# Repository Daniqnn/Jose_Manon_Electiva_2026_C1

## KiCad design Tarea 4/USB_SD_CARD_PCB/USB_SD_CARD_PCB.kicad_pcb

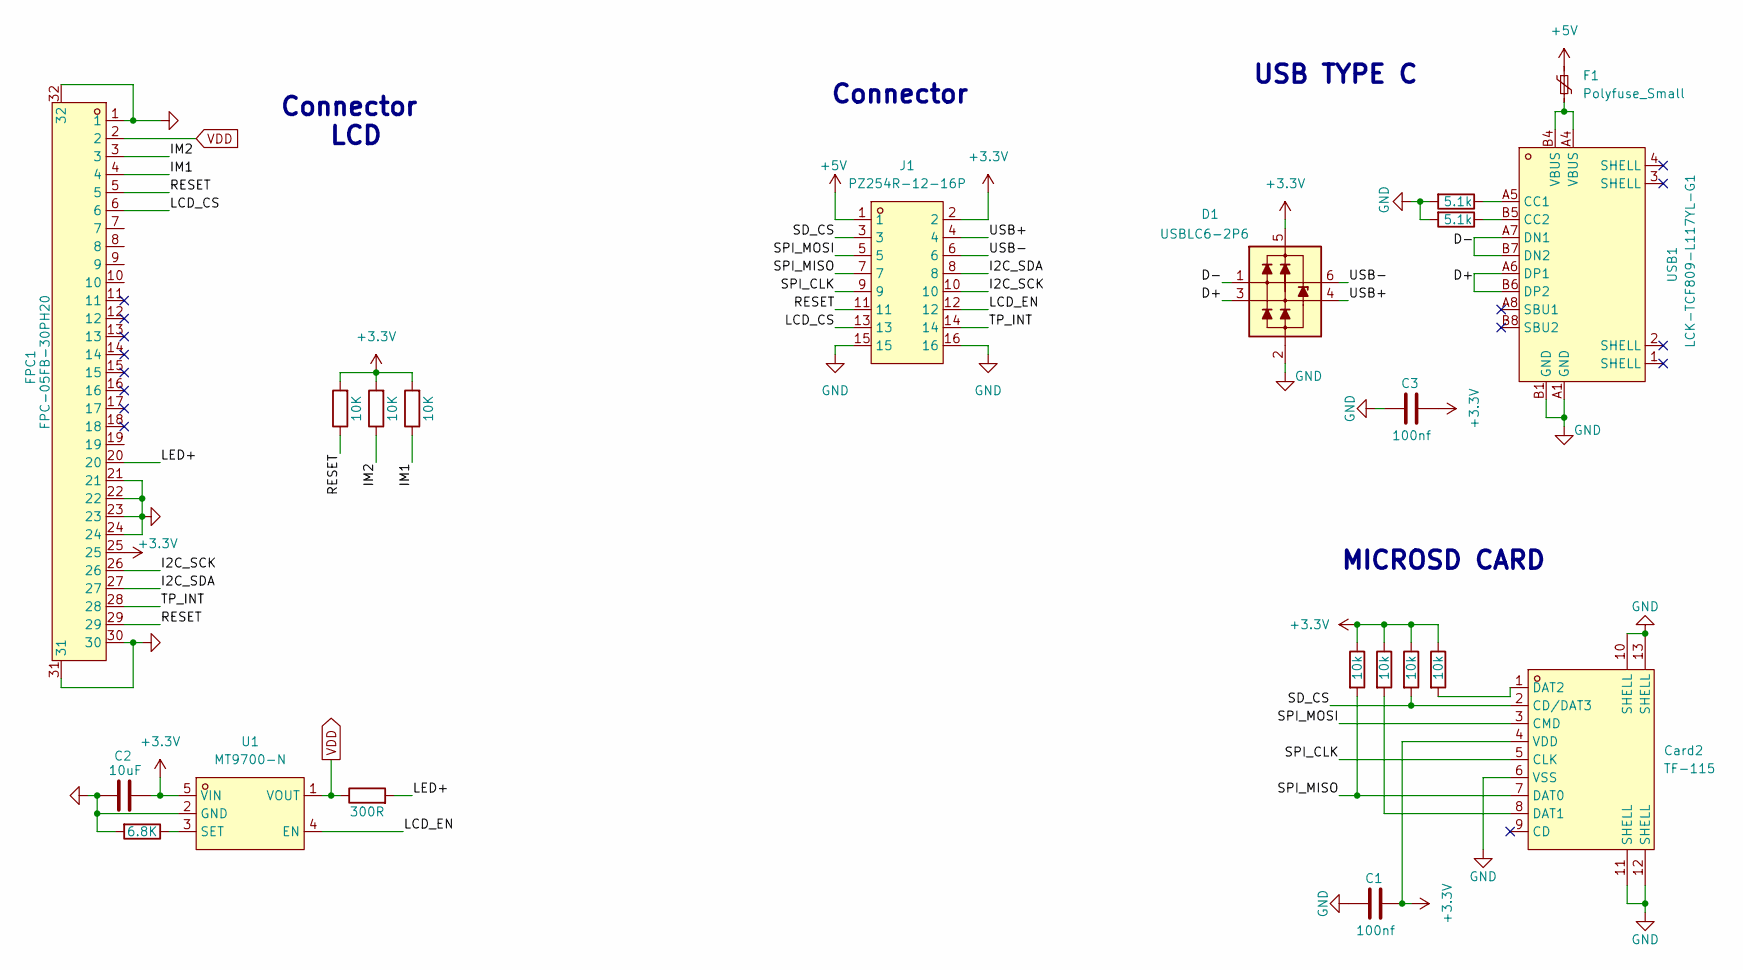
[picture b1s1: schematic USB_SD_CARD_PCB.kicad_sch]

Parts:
C1, C3: 100nf; C_0805_2012Metric; LCSC C710980
C2: 10uF; C_0201_0603Metric
Card2: TF-115; TF-SMD_TF-115; LCSC Part C266620
D1: USBLC6-2P6; SOT-666
F1: Polyfuse_Small; Fuse_0805_2012Metric
FPC1: FPC-05FB-30PH20; FPC-SMD_30P-P0.50_FPC-05FB-30PH20; LCSC Part C2856833
J1: PZ254R-12-16P; HDR-TH_16P-P2.54-H-M-R2-C8-S2.54; LCSC Part C492436
R1, R2: 5.1k; R_0805_2012Metric; LCSC C2930296
R3, R4, R5, R6: 10k; R_0603_1608Metric; LCSC C2930296
R7: 6.8K; R_0603_1608Metric; LCSC C2930296
R8: 300R; R_0603_1608Metric; LCSC C2930296
R9, R10, R11: 10K; R_0603_1608Metric; LCSC C2930296
U1: MT9700-N; SOT-23-5_L2.9-W1.6-P0.95-LS2.9-BL; LCSC Part C42441843
USB1: LCK-TCF809-L117YL-G1; USB-C-SMD_LCK-TCF809-L117YL-G1; LCSC Part C50380973

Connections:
+3.3V: C1.1, C2.1, C3.1, Card2.4 (VDD), D1.5 (VP), FPC1.25, J1.2, R3.1, R4.1, R5.1, R6.1, R9.2, R10.2, R11.2, U1.5 (VIN)
+5V: F1.1, J1.1
/D+: D1.3 (L2), USB1.A6 (DP1), USB1.B6 (DP2)
/D-: D1.1 (L1), USB1.A7 (DN1), USB1.B7 (DN2)
/I2C_SCK: FPC1.26, J1.10
/I2C_SDA: FPC1.27, J1.8
/IM1: FPC1.4, R11.1
/IM2: FPC1.3, R10.1
/LCD_CS: FPC1.6, J1.13
/LCD_EN: J1.12, U1.4 (EN)
/LED+: FPC1.20, R8.2
/RESET: FPC1.5, FPC1.29, J1.11, R9.1
/SD_CS: Card2.2 (CD/DAT3), J1.3, R4.2
/SPI_CLK: Card2.5 (CLK), J1.9
/SPI_MISO: Card2.7 (DAT0), J1.7, R6.2
/SPI_MOSI: Card2.3 (CMD), J1.5
/TP_INT: FPC1.28, J1.14
/USB+: D1.4 (L2), J1.4
/USB-: D1.6 (L1), J1.6
GND: C1.2, C2.2, C3.2, Card2.6 (VSS), Card2.10 (SHELL), Card2.11 (SHELL), Card2.12 (SHELL), Card2.13 (SHELL), D1.2 (VN), FPC1.1, FPC1.21, FPC1.22, FPC1.23, FPC1.24, FPC1.30, FPC1.31, FPC1.32, J1.15, J1.16, R1.2, R2.2, R7.2, U1.2 (GND), USB1.A1 (GND), USB1.B1 (GND)
unnamed: Card2.8 (DAT1), R5.2
unnamed: Card2.1 (DAT2), R3.2
unnamed: F1.2, USB1.A4 (VBUS), USB1.B4 (VBUS)
unnamed: R7.1, U1.3 (SET)
unnamed: R1.1, USB1.A5 (CC1)
unnamed: R2.1, USB1.B5 (CC2)
VDD: FPC1.2, R8.1, U1.1 (VOUT)

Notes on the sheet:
Connector LCD
USB TYPE C
MICROSD CARD
Connector

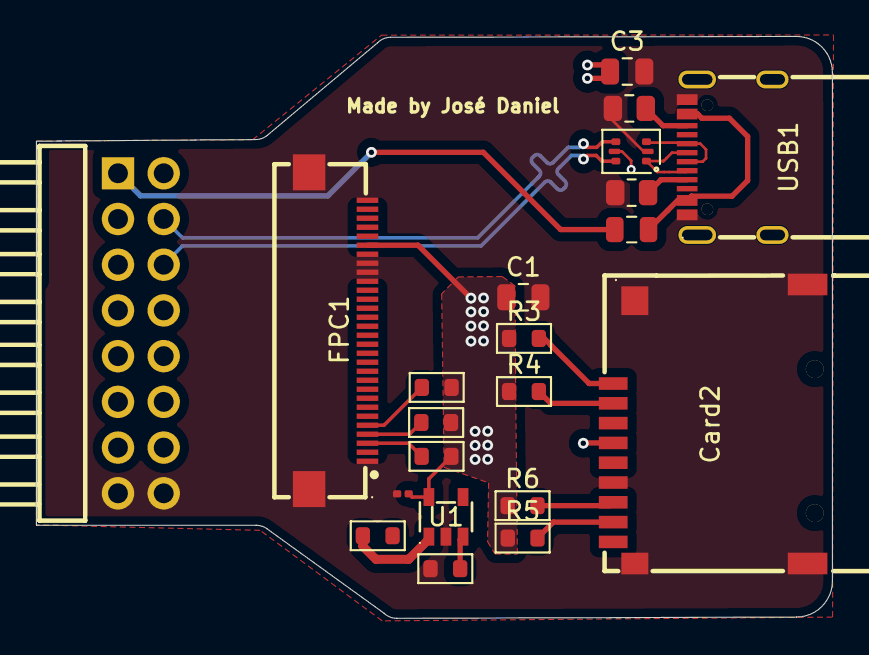
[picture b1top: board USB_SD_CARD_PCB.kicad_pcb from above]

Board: 4 copper layers, 44.2 x 32.3 mm, 21 parts (0 on the bottom side), 27 nets.

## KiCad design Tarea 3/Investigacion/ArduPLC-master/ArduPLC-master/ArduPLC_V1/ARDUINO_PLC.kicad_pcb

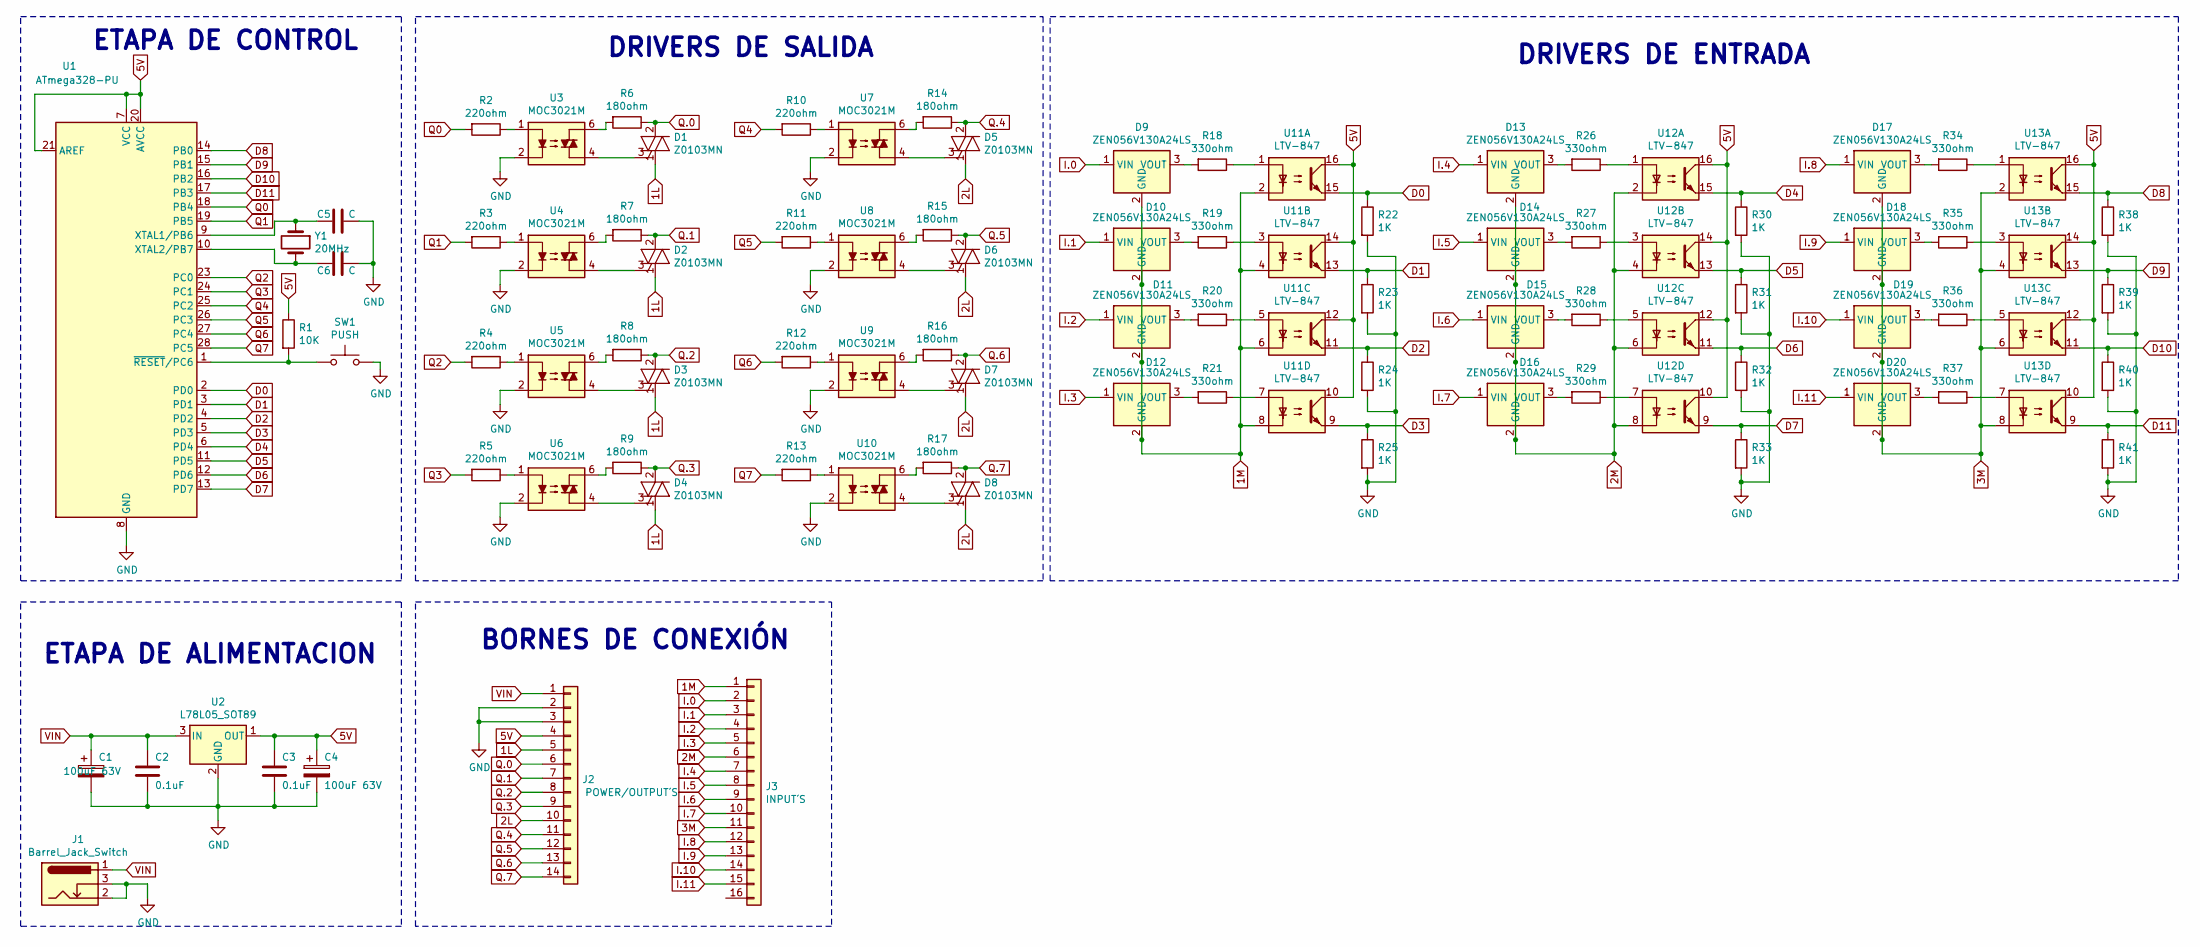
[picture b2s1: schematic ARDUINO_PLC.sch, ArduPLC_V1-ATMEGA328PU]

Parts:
C1, C4: 100uF 63V; CP_Radial_D8.0mm_P3.80mm
C2, C3: 0.1uF; C_Disc_D5.0mm_W2.5mm_P2.50mm
C5, C6: C; C_Disc_D5.0mm_W2.5mm_P2.50mm
D1, D2, D3, D4, D5, D6, D7, D8: Z0103MN; SOT-223
D9, D10, D11, D12, D13, D14, D15, D16, D17, D18, D19, D20: ZEN056V130A24LS; Littelfuse_PolyZen-LS
J1: Barrel_Jack_Switch; BarrelJack_Horizontal
J2: POWER/OUTPUT´S; Altech_AK300_1x14_P5.00mm_45-Degree
J3: INPUT´S; Altech_AK300_1x16_P5.00mm_45-Degree
R1: 10K; R_Axial_DIN0204_L3.6mm_D1.6mm_P1.90mm_Vertical
R2, R3, R4, R5, R10, R11, R12, R13: 220ohm; R_Axial_DIN0204_L3.6mm_D1.6mm_P1.90mm_Vertical
R6, R7, R8, R9, R14, R15, R16, R17: 180ohm; R_Axial_DIN0204_L3.6mm_D1.6mm_P1.90mm_Vertical
R18, R19, R20, R21, R26, R27, R28, R29, R34, R35, R36, R37: 330ohm; R_Axial_DIN0204_L3.6mm_D1.6mm_P1.90mm_Vertical
R22, R23, R24, R25, R30, R31, R32, R33, R38, R39, R40, R41: 1K; R_Axial_DIN0204_L3.6mm_D1.6mm_P1.90mm_Vertical
SW1: PUSH; Button_6mm
U1: ATmega328-PU; DIP-28_W7.62mm
U2: L78L05_SOT89; SOT-89-3
U3, U4, U5, U6, U7, U8, U9, U10: MOC3021M; DIP-6_W7.62mm_LongPads
U11, U12, U13: LTV-847; DIP-16_W7.62mm
Y1: 20MHz; Crystal_HC52-U_Vertical

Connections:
1L: D1.1 (A1), D2.1 (A1), D3.1 (A1), D4.1 (A1), J2.5
1M: D9.2 (GND), D10.2 (GND), D11.2 (GND), D12.2 (GND), J3.1, U11.2, U11.4, U11.6, U11.8
2L: D5.1 (A1), D6.1 (A1), D7.1 (A1), D8.1 (A1), J2.10
2M: D13.2 (GND), D14.2 (GND), D15.2 (GND), D16.2 (GND), J3.6, U12.2, U12.4, U12.6, U12.8
3M: D17.2 (GND), D18.2 (GND), D19.2 (GND), D20.2 (GND), J3.11, U13.2, U13.4, U13.6, U13.8
5V: C3.1, C4.1, J2.4, R1.1, U1.7 (VCC), U1.20 (AVCC), U1.21 (AREF), U2.1 (OUT), U11.10, U11.12, U11.14, U11.16, U12.10, U12.12, U12.14, U12.16, U13.10, U13.12, U13.14, U13.16
D0: R22.1, U1.2 (PD0), U11.15
D1: R23.1, U1.3 (PD1), U11.13
D2: R24.1, U1.4 (PD2), U11.11
D3: R25.1, U1.5 (PD3), U11.9
D4: R30.1, U1.6 (PD4), U12.15
D5: R31.1, U1.11 (PD5), U12.13
D6: R32.1, U1.12 (PD6), U12.11
D7: R33.1, U1.13 (PD7), U12.9
D8: R38.1, U1.14 (PB0), U13.15
D9: R39.1, U1.15 (PB1), U13.13
D10: R40.1, U1.16 (PB2), U13.11
D11: R41.1, U1.17 (PB3), U13.9
GND: C1.2, C2.2, C3.2, C4.2, C5.1, C6.1, J1.2, J1.3, J2.2, J2.3, R22.2, R23.2, R24.2, R25.2, R30.2, R31.2, R32.2, R33.2, R38.2, R39.2, R40.2, R41.2, SW1.2, U1.8 (GND), U1.22 (GND), U2.2 (GND), U3.2, U4.2, U5.2, U6.2, U7.2, U8.2, U9.2, U10.2
I.0: D9.1 (VIN), J3.2
I.1: D10.1 (VIN), J3.3
I.2: D11.1 (VIN), J3.4
I.3: D12.1 (VIN), J3.5
I.4: D13.1 (VIN), J3.7
I.5: D14.1 (VIN), J3.8
I.6: D15.1 (VIN), J3.9
I.7: D16.1 (VIN), J3.10
I.8: D17.1 (VIN), J3.12
I.9: D18.1 (VIN), J3.13
I.10: D19.1 (VIN), J3.14
I.11: D20.1 (VIN), J3.15
unnamed: C5.2, U1.9 (XTAL1/PB6), Y1.1
unnamed: C6.2, U1.10 (XTAL2/PB7), Y1.2
unnamed: D1.3 (G), U3.4
unnamed: D2.3 (G), U4.4
unnamed: D3.3 (G), U5.4
unnamed: D4.3 (G), U6.4
unnamed: D5.3 (G), U7.4
unnamed: D6.3 (G), U8.4
unnamed: D7.3 (G), U9.4
unnamed: D8.3 (G), U10.4
unnamed: D9.3 (VOUT), R18.2
unnamed: D10.3 (VOUT), R19.2
unnamed: D11.3 (VOUT), R20.2
unnamed: D12.3 (VOUT), R21.2
unnamed: D13.3 (VOUT), R26.2
unnamed: D14.3 (VOUT), R27.2
unnamed: D15.3 (VOUT), R28.2
unnamed: D16.3 (VOUT), R29.2
unnamed: D17.3 (VOUT), R34.2
unnamed: D18.3 (VOUT), R35.2
unnamed: D19.3 (VOUT), R36.2
unnamed: D20.3 (VOUT), R37.2
unnamed: R1.2, SW1.1, U1.1 (~RESET~/PC6)
unnamed: R2.1, U3.1
unnamed: R3.1, U4.1
unnamed: R4.1, U5.1
unnamed: R5.1, U6.1
unnamed: R6.2, U3.6
unnamed: R7.2, U4.6
unnamed: R8.2, U5.6
unnamed: R9.2, U6.6
unnamed: R10.1, U7.1
unnamed: R11.1, U8.1
unnamed: R12.1, U9.1
unnamed: R13.1, U10.1
unnamed: R14.2, U7.6
unnamed: R15.2, U8.6
unnamed: R16.2, U9.6
unnamed: R17.2, U10.6
unnamed: R18.1, U11.1
unnamed: R19.1, U11.3
unnamed: R20.1, U11.5
unnamed: R21.1, U11.7
unnamed: R26.1, U12.1
unnamed: R27.1, U12.3
unnamed: R28.1, U12.5
unnamed: R29.1, U12.7
unnamed: R34.1, U13.1
unnamed: R35.1, U13.3
unnamed: R36.1, U13.5
unnamed: R37.1, U13.7
Q0: R2.2, U1.18 (PB4)
Q1: R3.2, U1.19 (PB5)
Q2: R4.2, U1.23 (PC0)
Q3: R5.2, U1.24 (PC1)
Q4: R10.2, U1.25 (PC2)
Q5: R11.2, U1.26 (PC3)
Q6: R12.2, U1.27 (PC4)
Q7: R13.2, U1.28 (PC5)
Q.0: D1.2 (A2), D1.4 (A4), J2.6, R6.1
Q.1: D2.2 (A2), D2.4 (A4), J2.7, R7.1
Q.2: D3.2 (A2), D3.4 (A4), J2.8, R8.1
Q.3: D4.2 (A2), D4.4 (A4), J2.9, R9.1
Q.4: D5.2 (A2), D5.4 (A4), J2.11, R14.1
Q.5: D6.2 (A2), D6.4 (A4), J2.12, R15.1
Q.6: D7.2 (A2), D7.4 (A4), J2.13, R16.1
Q.7: D8.2 (A2), D8.4 (A4), J2.14, R17.1
VIN: C1.1, C2.1, J1.1, J2.1, U2.3 (IN)

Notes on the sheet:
ETAPA DE CONTROL
DRIVERS DE SALIDA
DRIVERS DE ENTRADA
ETAPA DE ALIMENTACION
BORNES DE CONEXIÓN

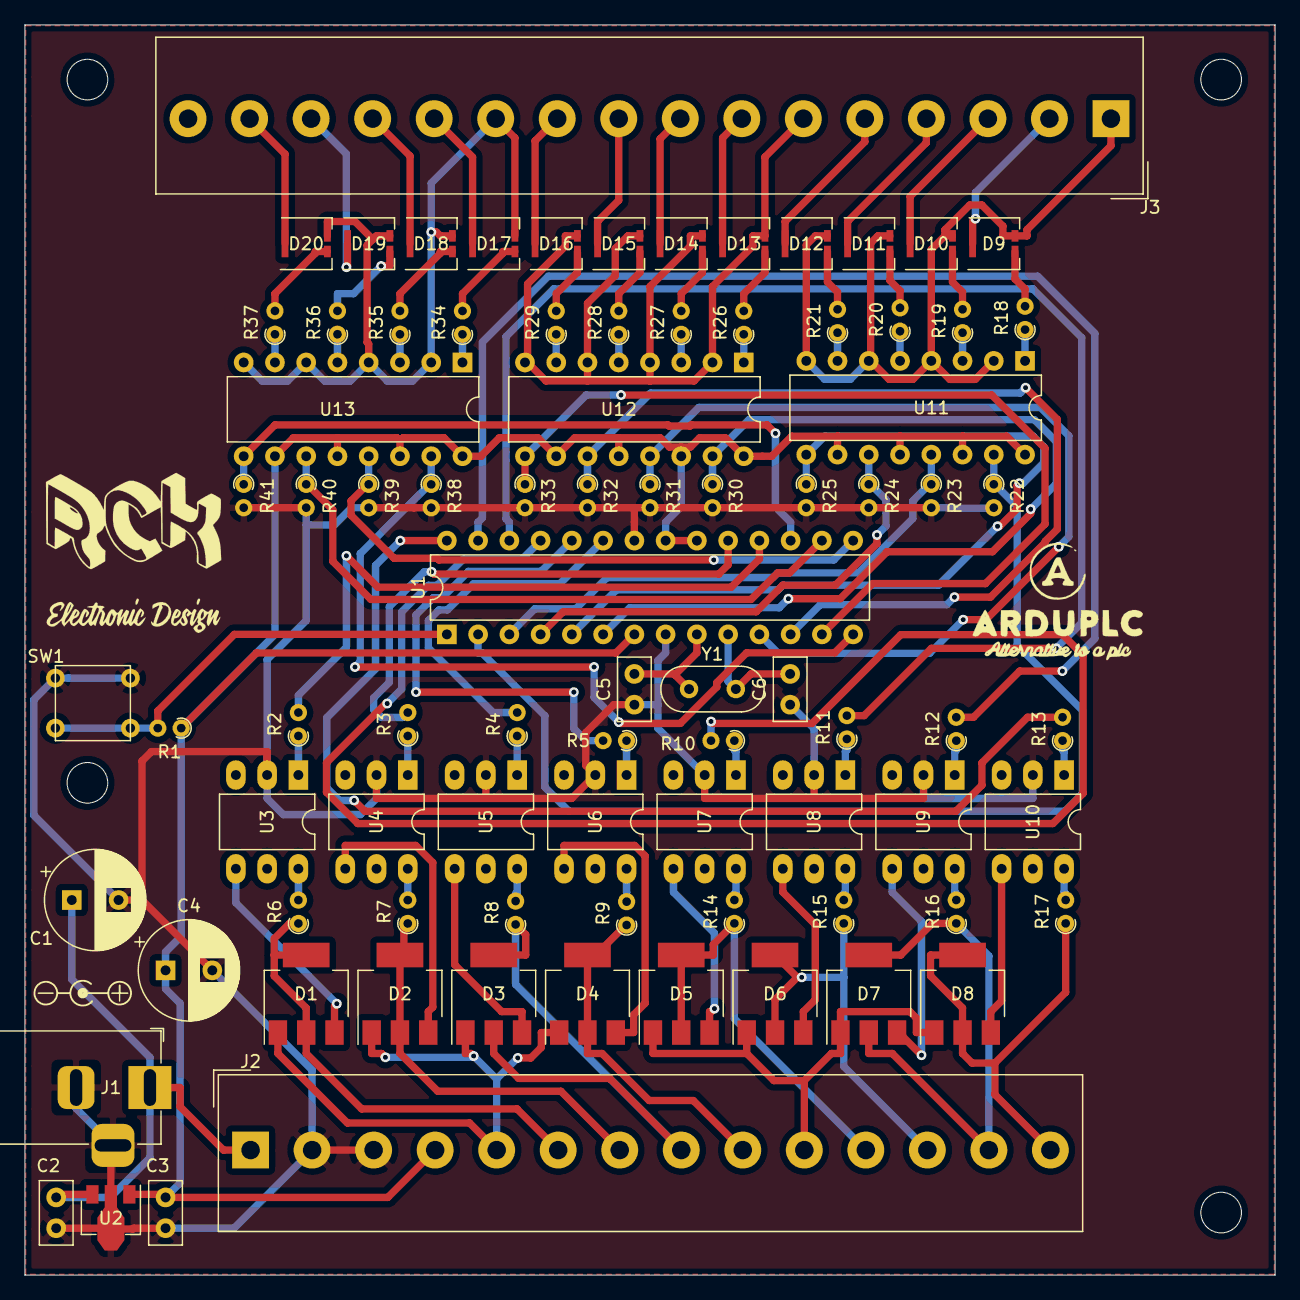
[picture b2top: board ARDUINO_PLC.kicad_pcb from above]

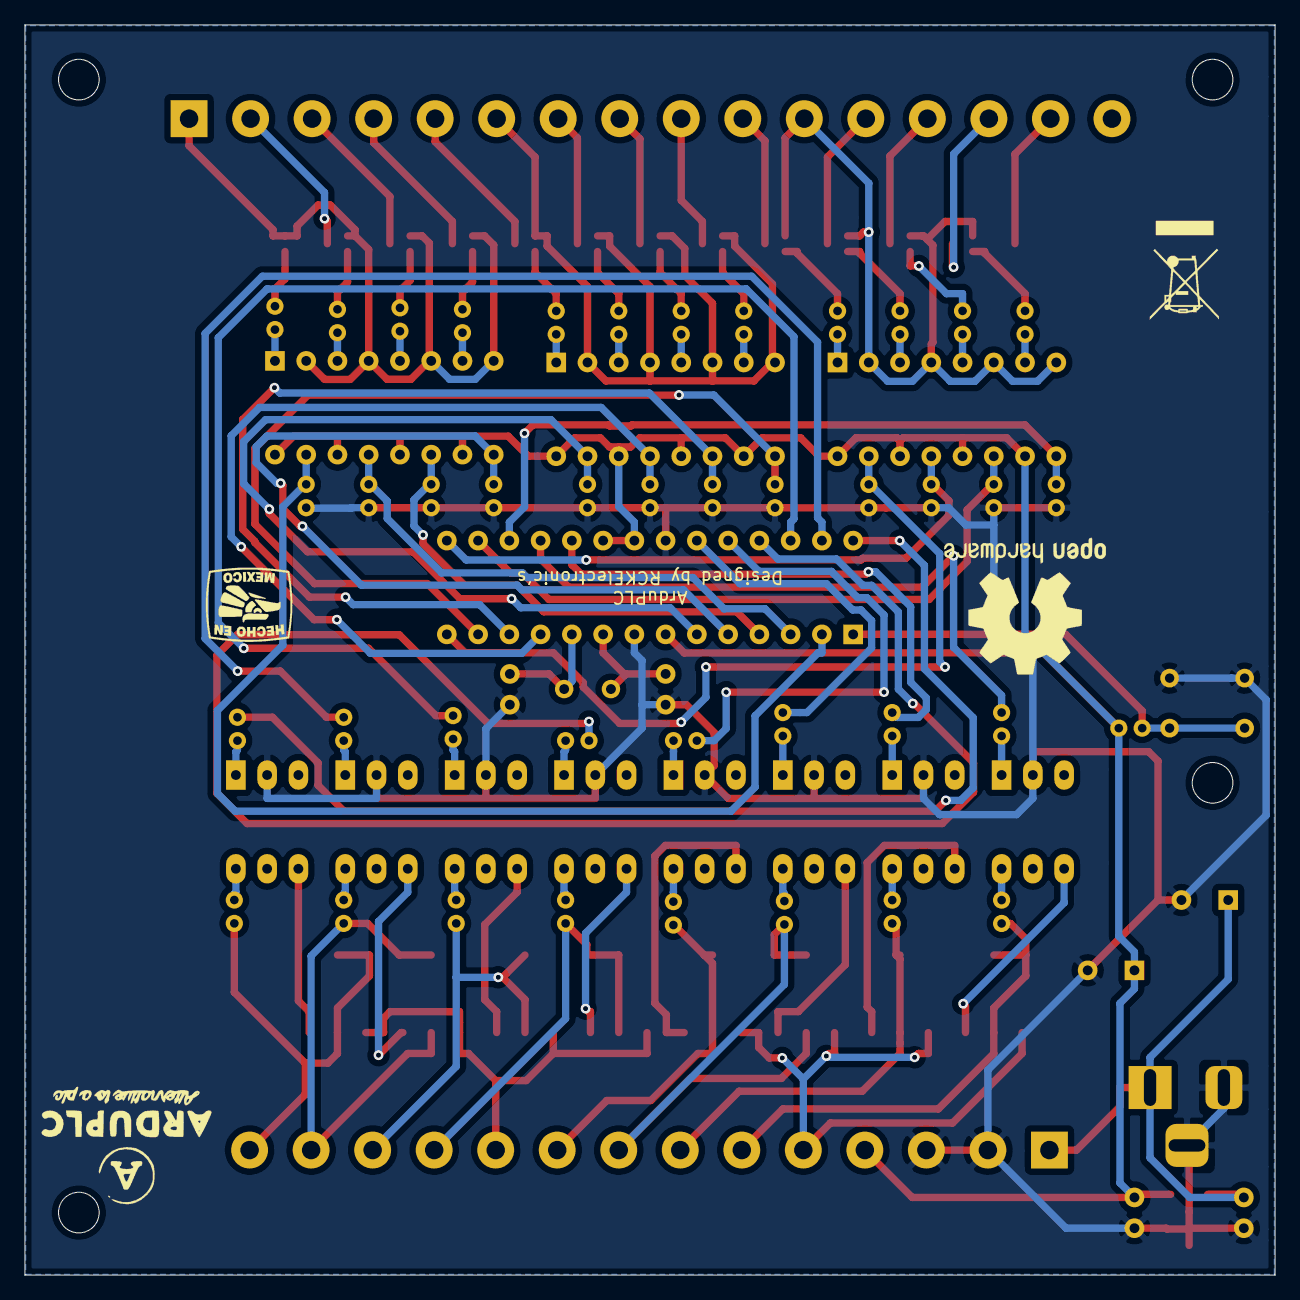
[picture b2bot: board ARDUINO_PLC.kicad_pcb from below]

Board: 2 copper layers, 101.6 x 101.6 mm, 89 parts (3 on the bottom side), 99 nets.

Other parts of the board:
G001: LOGO; echo_en_mexico
REF01: WEEE-Logo_5.6x8mm_SilkScreen
REF02: OSHW-Logo2_14.6x12mm_SilkScreen
REF03: Symbol_Barrel_Polarity

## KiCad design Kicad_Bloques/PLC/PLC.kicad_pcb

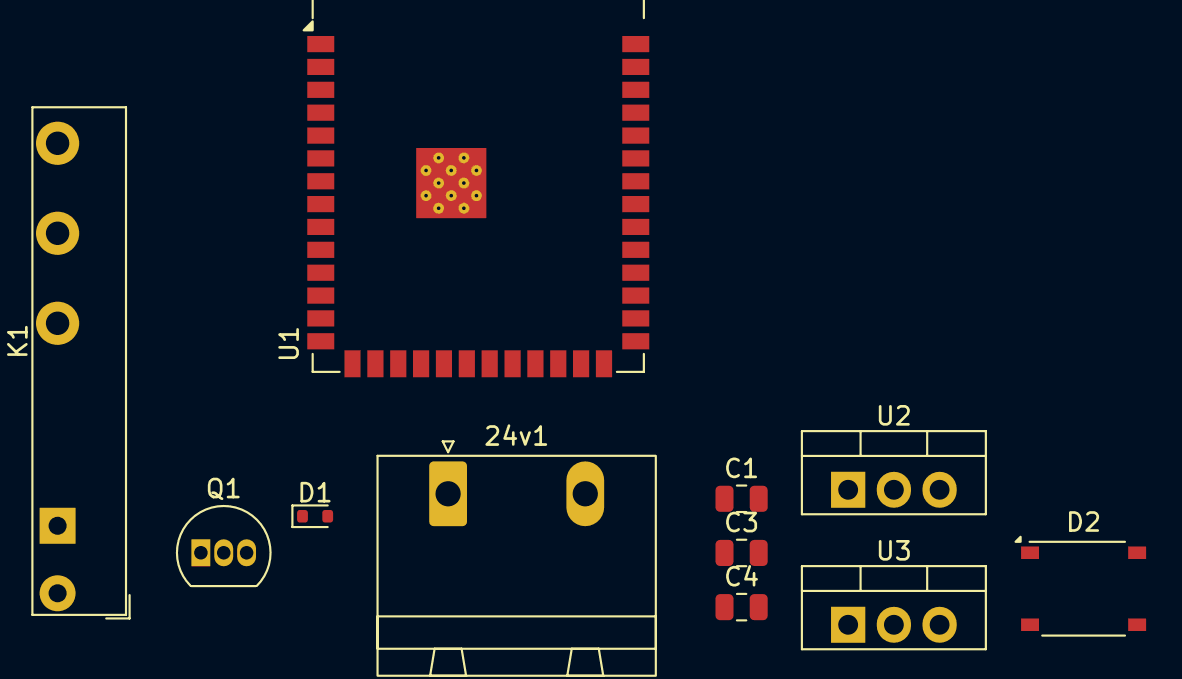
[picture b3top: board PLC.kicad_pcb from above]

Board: 2 copper layers, 11 parts (0 on the bottom side), 8 nets, no tracks yet.

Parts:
24v1: Conn_01x02_Pin; PhoenixContact_GMSTBA_2,5_2-G-7,62_1x02_P7.62mm_Horizontal
C1: 220nF; C_0805_2012Metric
C3: 330nF; C_0805_2012Metric
C4: 100nF; C_0805_2012Metric
D1: 1N4148WT; D_SOD-523
D2: ABS2; Diode_Bridge_Diotec_ABS
K1: FINDER-34.51; Relay_SPDT_Finder_34.51_Vertical
Q1: 2N3904; TO-92_Inline
U1: ESP32-S3-WROOM-1
U2: LM7805_TO220; TO-220-3_Vertical
U3: LM7812_TO220; TO-220-3_Vertical

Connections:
/5v: D1.1 (K), K1.A1, U2.3 (VO)
/12v: C4.1, U3.3 (VO)
/24v: C1.1, C3.1, D2.1 (+), K1.11, U2.1 (VI), U3.1 (VI)
GND: C1.2, C3.2, C4.2, D2.2 (-), Q1.1 (E), U2.2 (GND), U3.2 (GND)
unnamed: 24v1.1, D2.4
unnamed: 24v1.2, D2.3
unnamed: D1.2 (A), K1.A2, Q1.3 (C)
unnamed: U1.1 (GND), U1.40 (GND), U1.41 (GND)

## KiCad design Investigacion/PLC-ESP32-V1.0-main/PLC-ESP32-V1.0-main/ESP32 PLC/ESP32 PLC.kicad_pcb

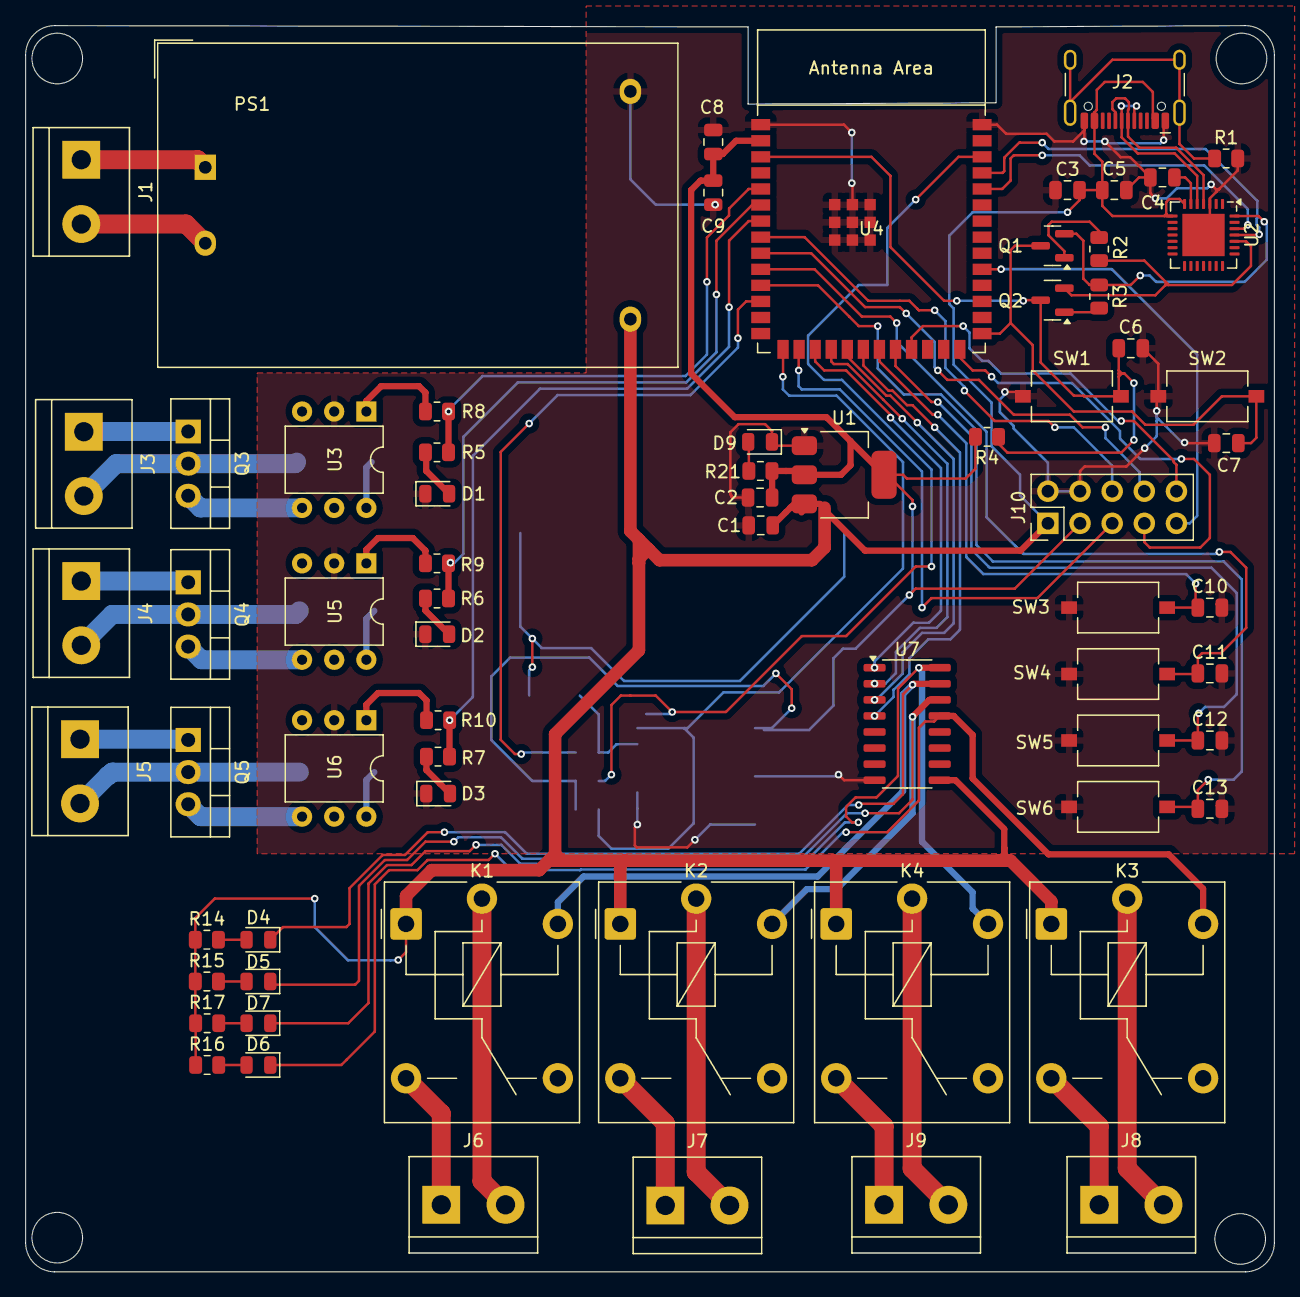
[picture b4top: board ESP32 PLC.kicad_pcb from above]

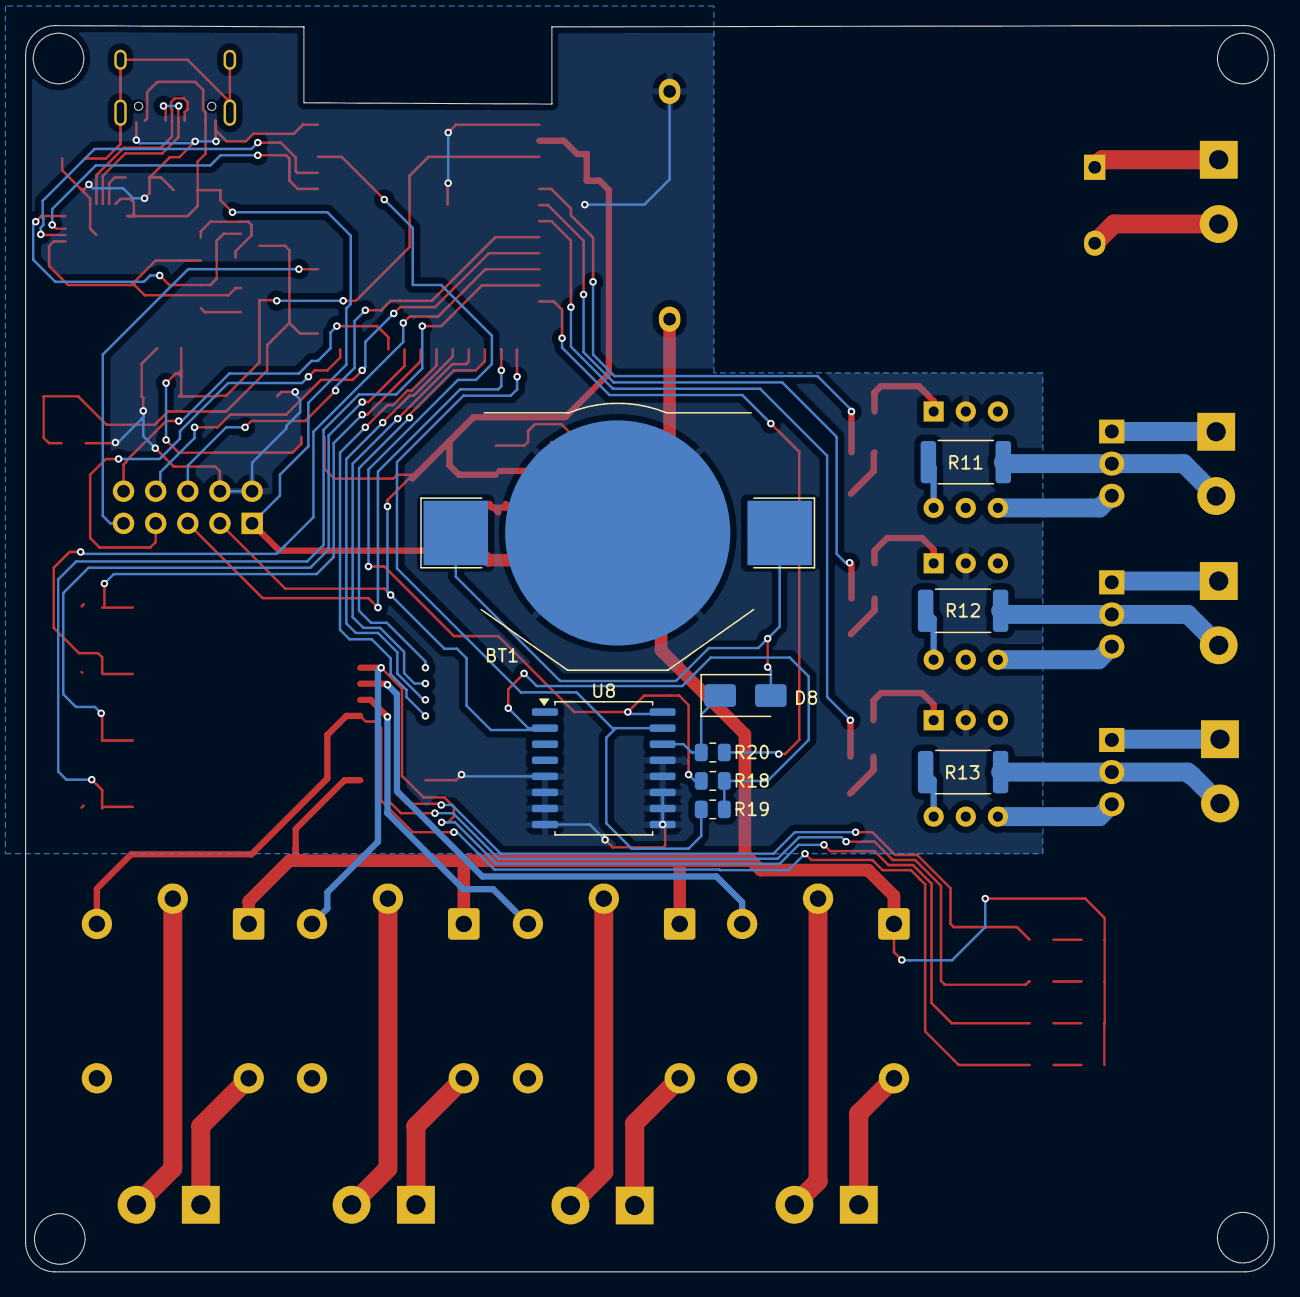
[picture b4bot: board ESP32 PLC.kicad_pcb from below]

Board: 2 copper layers, 98.7 x 98.5 mm, 78 parts (9 on the bottom side), 74 nets.

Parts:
BT1: Battery_Cell; BatteryHolder_Keystone_3002_1x2032
C1, C9: 10uF; C_0805_2012Metric
C2: 22uF; C_0805_2012Metric
C3: 4.7uF; C_0805_2012Metric
C4, C5: 100nF; C_0805_2012Metric
C6, C7, C8, C10, C11, C12, C13: 0.1uF; C_0805_2012Metric
D1, D2, D3, D4, D5, D6, D7, D9: LED; LED_0805_2012Metric
D8: 1N47xxA; D_SMA
J1: AC INPUT; TerminalBlock_bornier-2_P5.08mm
J2: USB_C_Receptacle_USB2.0_14P; USB_C_Receptacle_HCTL_HC-TYPE-C-16P-01A
J3, J4, J5, J6, J7, J8, J9: Screw_Terminal_01x02; TerminalBlock_bornier-2_P5.08mm
J10: Conn_02x05_Odd_Even; PinHeader_2x05_P2.54mm_Vertical
K1, K2, K3, K4: FINDER-36.11; Relay_SPDT_Finder_36.11
PS1: HLK-5M05; Converter_ACDC_Hi-Link_HLK-5Mxx
Q1, Q2: S8050; SOT-23
Q3, Q4, Q5: BTA16-600B; TO-220-3_Vertical
R1: 1M; R_0805_2012Metric
R2, R3: 150; R_0805_2012Metric
R4: 10k; R_0805_2012Metric
R5, R6, R7: 100; R_0805_2012Metric
R8, R9, R10: 1k; R_0805_2012Metric
R11, R12, R13: 470; R_2512_6332Metric
R14, R15, R16, R17: 470; R_0805_2012Metric
R18, R19: 4.7k; R_0805_2012Metric
R20: 100k; R_0805_2012Metric
R21: 330; R_0805_2012Metric
SW1, SW2, SW3, SW4, SW5, SW6: SW_Push; SW_Tactile_SPST_NO_Straight_CK_PTS636Sx25SMTRLFS
U1: AZ1117-3.3; SOT-223-3_TabPin2
U2: CP2102N-Axx-xQFN28; QFN-28-1EP_5x5mm_P0.5mm_EP3.35x3.35mm
U3, U5, U6: MOC3021M; DIP-6_W7.62mm
U4: ESP32-S3-WROOM-1
U7: ULN2003; SO-16_3.9x9.9mm_P1.27mm
U8: DS3231M; SOIC-16W_7.5x10.3mm_P1.27mm

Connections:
3.3V: C2.1, C8.1, C9.1, J10.3, R4.2, R18.2, R19.1, R21.1, U1.2 (VO), U4.2 (3V3), U8.2 (VCC)
5V: C1.1, C3.1, C5.1, J2.A4 (VBUS), J2.A9 (VBUS), J2.B4 (VBUS), J2.B9 (VBUS), J10.1, K1.A1, K2.A1, K3.A1, K4.A1, PS1.4 (+Vout), R14.1, R15.1, R16.1, R17.1, U1.3 (VI), U2.7 (VREGIN), U2.8 (VBUS), U7.9 (COM)
/BUTTONS/GPIO13 - PB1: C10.1, SW3.2, U4.21 (GPIO13/TOUCH13/ADC2_CH2/FSPIQ/FSPIIO7/S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)
/BUTTONS/GPIO14 - PB2: C12.1, SW5.2, U4.22 (GPIO14/TOUCH14/ADC2_CH3/FSPIWP/FSPIDQS/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)
/BUTTONS/GPIO17 - PB3: C11.1, SW4.2, U4.10 (GPIO17/U1TXD/ADC2_CH6)
/BUTTONS/GPIO18 - PB4: C13.1, SW6.2, U4.11 (GPIO18/U1RXD/ADC2_CH7/CLK_OUT3)
/ESP32 S3/GPIO2 -SCL: R18.1, U4.38 (GPIO2/TOUCH2/ADC1_CH1), U8.16 (SCL)
/ESP32 S3/GPIO3 -SDA: R19.2, U4.15 (GPIO3/TOUCH3/ADC1_CH2), U8.15 (SDA)
/ESP32 S3/GPIO5 - SSR1: R5.2, R8.2, U4.5 (GPIO5/TOUCH5/ADC1_CH4)
/ESP32 S3/GPIO6 - SSR2: R6.2, R9.2, U4.6 (GPIO6/TOUCH6/ADC1_CH5)
/ESP32 S3/GPIO7 - SSR2: R7.2, R10.2, U4.7 (GPIO7/TOUCH7/ADC1_CH6)
/ESP32 S3/GPIO8 - RTC: R20.1, U4.12 (GPIO8/TOUCH8/ADC1_CH7/SUBSPICS1)
/ESP32 S3/GPIO9 - RELAY1: U4.17 (GPIO9/TOUCH9/ADC1_CH8/FSPIHD/SUBSPIHD), U7.1 (I1)
/ESP32 S3/GPIO10 - RELAY2: U4.18 (GPIO10/TOUCH10/ADC1_CH9/FSPICS0/FSPIIO4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), U7.2 (I2)
/ESP32 S3/GPIO11 - RELAY3: U4.19 (GPIO11/TOUCH11/ADC2_CH0/FSPID/FSPIIO5/S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), U7.3 (I3)
/ESP32 S3/GPIO12 - RELAY4: U4.20 (GPIO12/TOUCH12/ADC2_CH1/FSPICLK/FSPIIO6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), U7.4 (I4)
/ESP32 S3/RX: U2.26 (TXD), U4.36 (U0RXD/GPIO44/CLK_OUT2)
/ESP32 S3/TX: U2.25 (RXD), U4.37 (U0TXD/GPIO43/CLK_OUT1)
BOOT: C7.1, Q1.3 (C), SW2.2, U4.27 (GPIO0/BOOT)
GND: BT1.2 (-), C1.2, C2.2, C3.2, C4.2, C5.2, C6.2, C7.2, C8.2, C9.2, C10.2, C11.2, C12.2, C13.2, D1.1 (K), D2.1 (K), D3.1 (K), D9.1 (K), J2.A1 (GND), J2.A12 (GND), J2.B1 (GND), J2.B12 (GND), J10.2, J10.4, PS1.3 (-Vout), R1.2, SW1.1, SW2.1, SW3.1, SW4.1, SW5.1, SW6.1, U1.1 (GND), U2.3 (GND), U2.29 (GND), U3.2, U4.1 (GND), U4.40 (GND), U4.41 (GND), U5.2, U6.2, U7.8 (GND), U8.5 (GND), U8.6 (GND), U8.7 (GND), U8.8 (GND), U8.9 (GND), U8.10 (GND), U8.11 (GND), U8.12 (GND), U8.13 (GND)
GPIO15: J10.6, U4.8 (GPIO15/U0RTS/ADC2_CH4/XTAL_32K_P)
GPIO16: J10.8, U4.9 (GPIO16/U0CTS/ADC2_CH5/XTAL_32K_N)
GPIO21: J10.10, U4.23 (GPIO21)
GPIO38: J10.9, U4.31 (GPIO38/FSPIWP/SUBSPIWP)
GPIO45: J10.7, U4.26 (GPIO45)
GPIO46: J10.5, U4.16 (GPIO46)
unnamed: BT1.1 (+), D8.2 (A)
unnamed: D1.2 (A), R5.1
unnamed: D2.2 (A), R6.1
unnamed: D3.2 (A), R7.1
unnamed: D4.2 (A), R14.2
unnamed: D5.2 (A), R15.2
unnamed: D6.2 (A), R16.2
unnamed: D7.2 (A), R17.2
unnamed: D8.1 (K), R20.2, U8.14 (VBAT)
unnamed: D9.2 (A), R21.2
unnamed: J1.1, PS1.1 (AC/L)
unnamed: J1.2, PS1.2 (AC/N)
unnamed: J2.S1 (SHIELD), R1.1
unnamed: J3.1, Q3.1 (A1)
unnamed: J3.2, Q3.2 (A2), R11.1
unnamed: J4.1, Q4.1 (A1)
unnamed: J4.2, Q4.2 (A2), R12.1
unnamed: J5.1, Q5.1 (A1)
unnamed: J5.2, Q5.2 (A2), R13.1
unnamed: J6.1, K1.14
unnamed: J6.2, K1.11
unnamed: J7.1, K2.14
unnamed: J7.2, K2.11
unnamed: J8.1, K3.14
unnamed: J8.2, K3.11
unnamed: J9.1, K4.14
unnamed: J9.2, K4.11
unnamed: Q1.1 (B), R2.2
unnamed: Q1.2 (E), R3.1, U2.28 (~DTR)
unnamed: Q2.1 (B), R3.2
unnamed: Q2.2 (E), R2.1, U2.24 (~RTS)
unnamed: Q3.3 (G), U3.4
unnamed: Q4.3 (G), U5.4
unnamed: Q5.3 (G), U6.4
unnamed: R8.1, U3.1
unnamed: R9.1, U5.1
unnamed: R10.1, U6.1
unnamed: R11.2, U3.6
unnamed: R12.2, U5.6
unnamed: R13.2, U6.6
unnamed: J2.A6 (D+), J2.B6 (D+), U2.4 (D+)
unnamed: J2.A7 (D-), J2.B7 (D-), U2.5 (D-)
unnamed: C4.1, U2.6 (VDD)
RELAY1: D7.1 (K), K4.A2, U7.16 (O1)
RELAY2: D4.1 (K), K1.A2, U7.15 (O2)
RELAY3: D5.1 (K), K2.A2, U7.14 (O3)
RELAY4: D6.1 (K), K3.A2, U7.13 (O4)
RESET: C6.1, Q2.3 (C), R4.1, SW1.2, U4.3 (EN)

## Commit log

2026-01-23 Primer commit
2026-01-23 Version 1
2026-01-23 Resumen version 1
2026-02-03 Diseño FreeCad
2026-02-03 Actualizacion Documento PLC
2026-02-03 Actualizacion SolidEdge
2026-02-03 Documento PLC
2026-02-03 Orden
2026-02-08 Bloques kicad
2026-02-09 Actualizacion bloques 9/2/2026{
2026-02-11 Actualizacion Bloques e Investigacion
2026-02-11 Bloque Analogico
2026-02-13 Actualizacion bloque 4-20mA
2026-02-17 Actualizacion de bloques
2026-03-08 Ordenando Repositorio
2026-03-08 Organizando
2026-03-09 Tarea 4
2026-03-12 USB type c Conexiones
2026-03-21 USB CARD Y SD
2026-04-18 Actualizacion 18/04/26
